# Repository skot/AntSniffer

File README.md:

# The Anteater
This is a upgrade to the AntSniffer with a FT4232 usbserial IC on it so you can read hashboard serial and I2C packets directly over USB.

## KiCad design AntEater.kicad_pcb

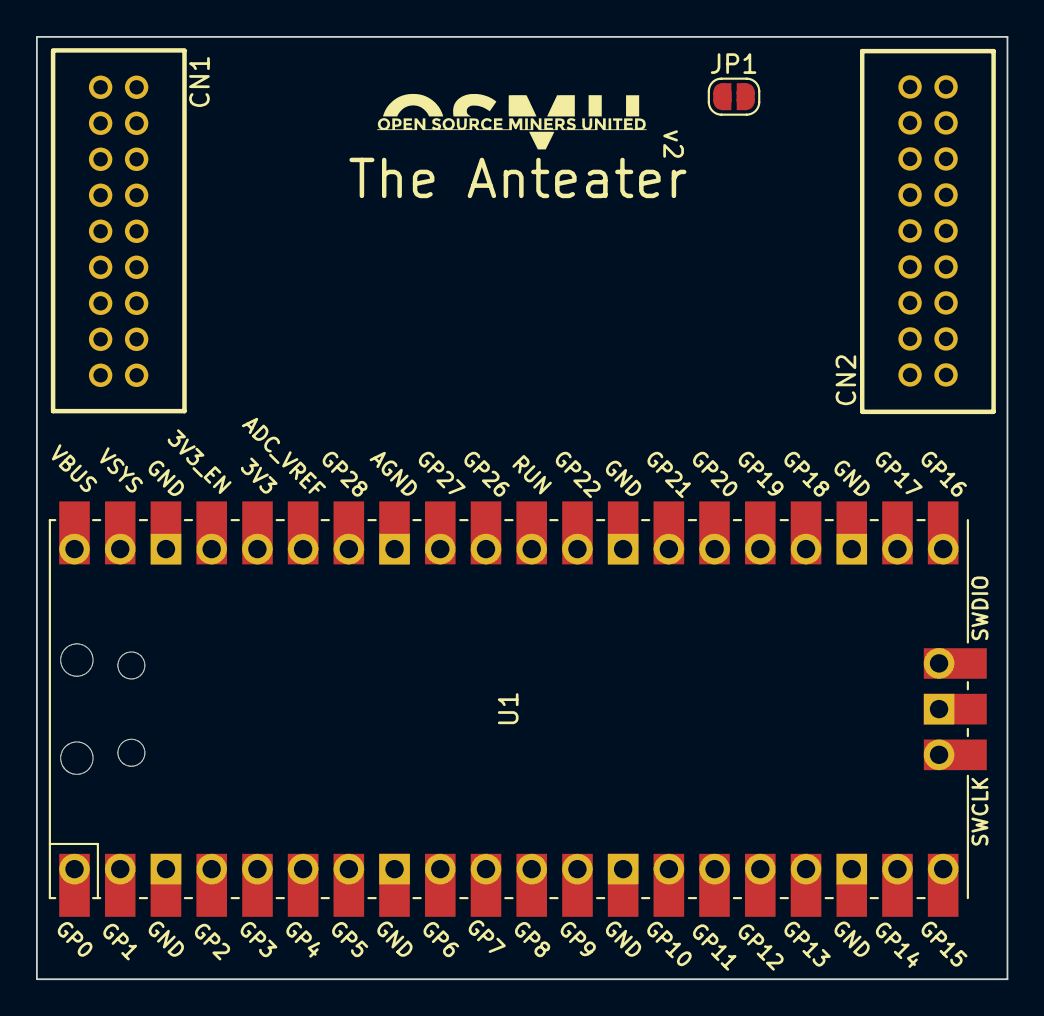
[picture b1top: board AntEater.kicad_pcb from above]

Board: 4 copper layers, 53.9 x 52.3 mm, 5 parts (0 on the bottom side), 12 nets, no tracks yet.

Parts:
CN1, CN2: X2026WRS-2X09D-LPSW; CONN-TH_X2026WV-2-09D-46SN
Ge: LOGO
JP1: SolderJumper_2_Open; SolderJumper-2_P1.3mm_Open_RoundedPad1.0x1.5mm
U1: Pico; RPi_Pico_SMD_TH

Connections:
/3V3: JP1.1 (A), U1.36 (3V3)
/A0: CN1.7, CN2.11
/A1: CN1.8, CN2.12
/A2: CN1.5, CN2.13
/GND: CN1.1, CN1.2, CN1.9, CN1.10, CN1.13, CN1.14, CN2.5, CN2.6, CN2.9, CN2.10, CN2.17, CN2.18, U1.3 (GND), U1.8 (GND), U1.13 (GND), U1.18 (GND), U1.23 (GND), U1.28 (GND), U1.33 (AGND), U1.38 (GND)
/HB_3V3: CN1.15, CN2.3, JP1.2 (B)
/PLUG: CN1.6, CN2.14, U1.7 (GPIO5)
/RST: CN1.16, CN2.4, U1.6 (GPIO4)
/RX: CN1.11, CN2.7, U1.10 (GPIO7)
/SCL: CN1.3, CN2.15, U1.5 (GPIO3)
/SDA: CN1.4, CN2.16, U1.4 (GPIO2)
/TX: CN1.12, CN2.8, U1.9 (GPIO6)

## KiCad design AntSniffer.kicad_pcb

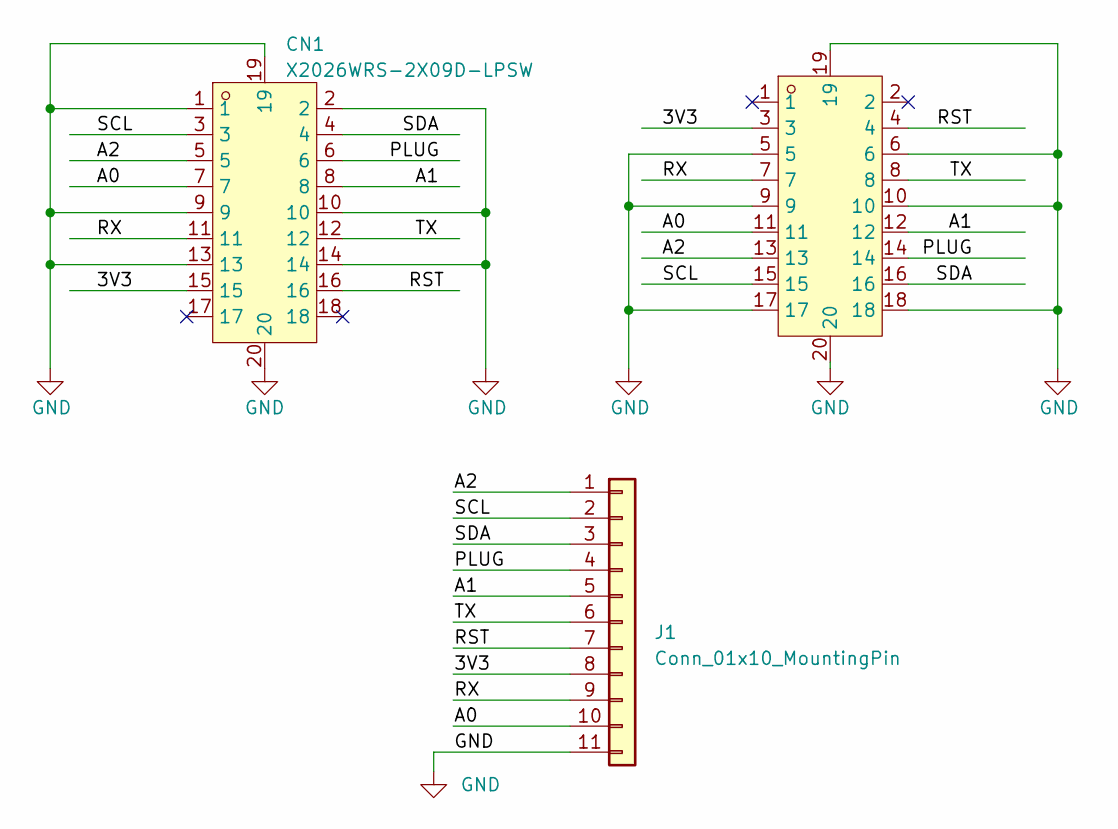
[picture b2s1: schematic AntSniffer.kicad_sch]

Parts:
CN1, CN2: X2026WRS-2X09D-LPSW; CONN-SMD_X2026WRS-2X09D-LPSW; LCSC Part C718164
J1: Conn_01x10_MountingPin; PinHeader_1x11_P2.54mm_Vertical

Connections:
/3V3: CN1.15, CN2.3, J1.8
/A0: CN1.7, CN2.11, J1.10
/A1: CN1.8, CN2.12, J1.5
/A2: CN1.5, CN2.13, J1.1
/PLUG: CN1.6, CN2.14, J1.4
/RST: CN1.16, CN2.4, J1.7
/RX: CN1.11, CN2.7, J1.9
/SCL: CN1.3, CN2.15, J1.2
/SDA: CN1.4, CN2.16, J1.3
/TX: CN1.12, CN2.8, J1.6
GND: CN1.1, CN1.2, CN1.9, CN1.10, CN1.13, CN1.14, CN1.19, CN1.20, CN2.5, CN2.6, CN2.9, CN2.10, CN2.17, CN2.18, CN2.19, CN2.20, J1.11

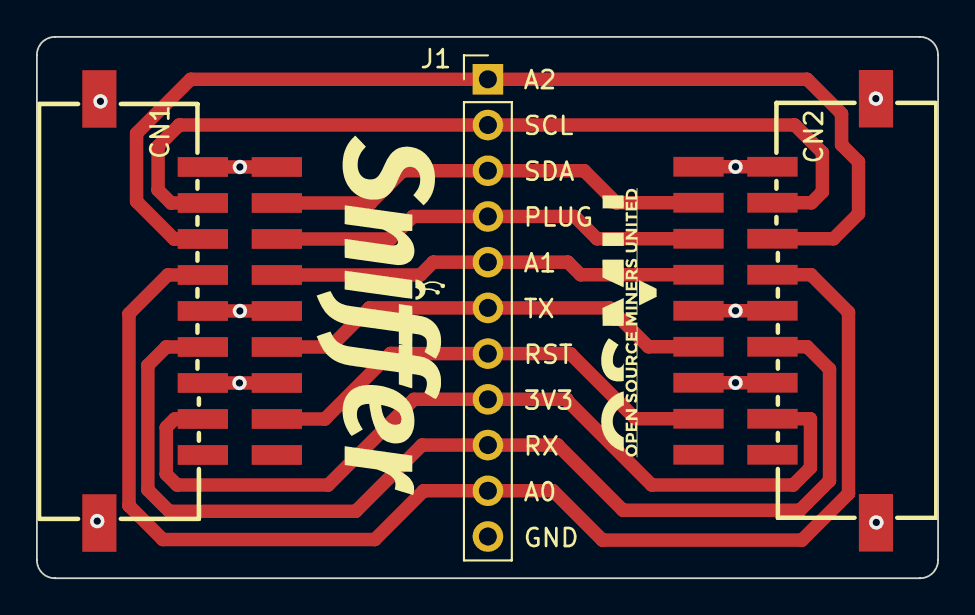
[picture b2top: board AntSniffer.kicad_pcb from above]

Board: 2 copper layers, 50.1 x 30.1 mm, 4 parts (0 on the bottom side), 11 nets.

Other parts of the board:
Ge: LOGO

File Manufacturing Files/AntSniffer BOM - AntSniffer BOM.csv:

Component Count:,4,,,,,,,
Item,Qty,Reference(s),Value,LibPart,Footprint,Datasheet,DNP,LCSC Part
1,2,"CN1, CN2",X2026WRS-2X09D-LPSW,x2026:X2026WRS-2X09D-LPSW,EASYEDA2KICAD:CONN-SMD_X2026WRS-2X09D-LPSW,https://datasheet.lcsc.com/lcsc/2110111530_XKB-Connectivity-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,,C718164
2,1,D1,LED,Device:LED,LED_SMD:LED_0603_1608Metric,https://datasheet.lcsc.com/lcsc/2008201032_Foshan-NationStar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,,C84263
3,1,J1,Conn_01x10_MountingPin,Connector_Generic_MountingPin:Conn_01x10_MountingPin,Connector_PinHeader_2.54mm:PinHeader_1x10_P2.54mm_Vertical,https://datasheet.lcsc.com/lcsc/2307210925_XKB-Connectivity-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,,C706882

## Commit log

2023-11-04 Upload V1
    Upload V1
2023-11-04 Added BOM and example 3D render
2023-11-06 switched to two layer board. added GND pin
2023-11-06 moved libraries local, updated render, generated BOM and manufacturing files
2023-11-06 checked gerbers ✅
2024-01-11 added data cable pinout doc
2024-03-20 renamed project
2024-03-20 placed and routed
2024-03-20 add gitignore
2024-03-20 added an optional voltage regulator. DRC passed. generated gerbers
2024-04-01 add iBOM for assembly
2024-04-02 cleanup
2024-04-02 switched schematic to RP2040
2024-04-02 switched to RPi Pico
